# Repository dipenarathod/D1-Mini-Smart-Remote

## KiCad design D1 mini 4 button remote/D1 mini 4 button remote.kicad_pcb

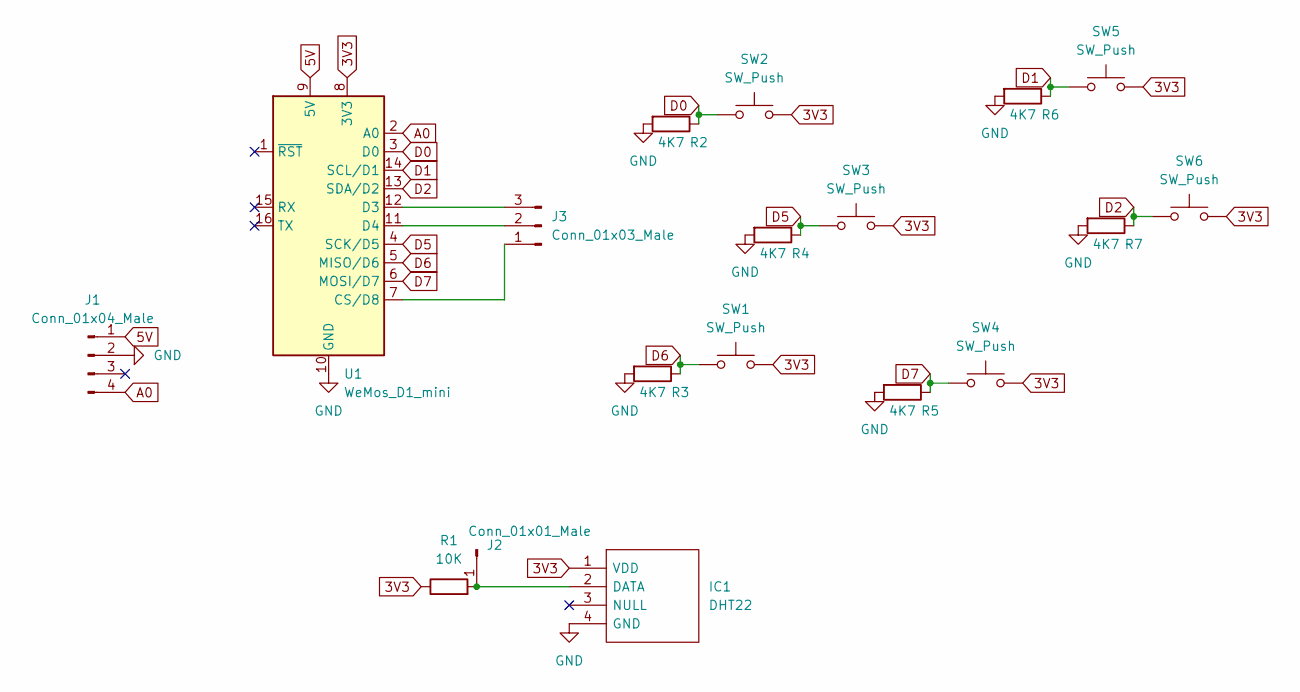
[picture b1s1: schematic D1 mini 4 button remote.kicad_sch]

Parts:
IC1: DHT22; Manufacturer_Part_Number DHT22
J1: Conn_01x04_Male; PinHeader_1x04_P2.54mm_Vertical
J2: Conn_01x01_Male; PinHeader_1x01_P2.54mm_Vertical
J3: Conn_01x03_Male; PinHeader_1x03_P2.54mm_Vertical
R1: 10K; R_Axial_DIN0207_L6.3mm_D2.5mm_P7.62mm_Horizontal
R2, R3, R4, R5, R6, R7: 4K7; R_Axial_DIN0207_L6.3mm_D2.5mm_P7.62mm_Horizontal
SW1, SW2, SW3, SW4, SW5, SW6: SW_Push; SW_PUSH_6mm
U1: WeMos_D1_mini; WEMOS_D1_mini_light

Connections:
3V3: IC1.1 (VDD), R1.1, SW1.2, SW2.2, SW3.2, SW4.2, SW5.2, SW6.2, U1.8 (3V3)
5V: J1.1, U1.9 (5V)
A0: J1.4, U1.2 (A0)
D0: R2.1, SW2.1, U1.3 (D0)
D1: R6.1, SW5.1, U1.14 (SCL/D1)
D2: R7.1, SW6.1, U1.13 (SDA/D2)
D5: R4.1, SW3.1, U1.4 (SCK/D5)
D6: R3.1, SW1.1, U1.5 (MISO/D6)
D7: R5.1, SW4.1, U1.6 (MOSI/D7)
GND: IC1.4 (GND), J1.2, R2.2, R3.2, R4.2, R5.2, R6.2, R7.2, U1.10 (GND)
unnamed: IC1.2 (DATA), J2.1, R1.2
unnamed: J3.1, U1.7 (CS/D8)
unnamed: J3.2, U1.11 (D4)
unnamed: J3.3, U1.12 (D3)

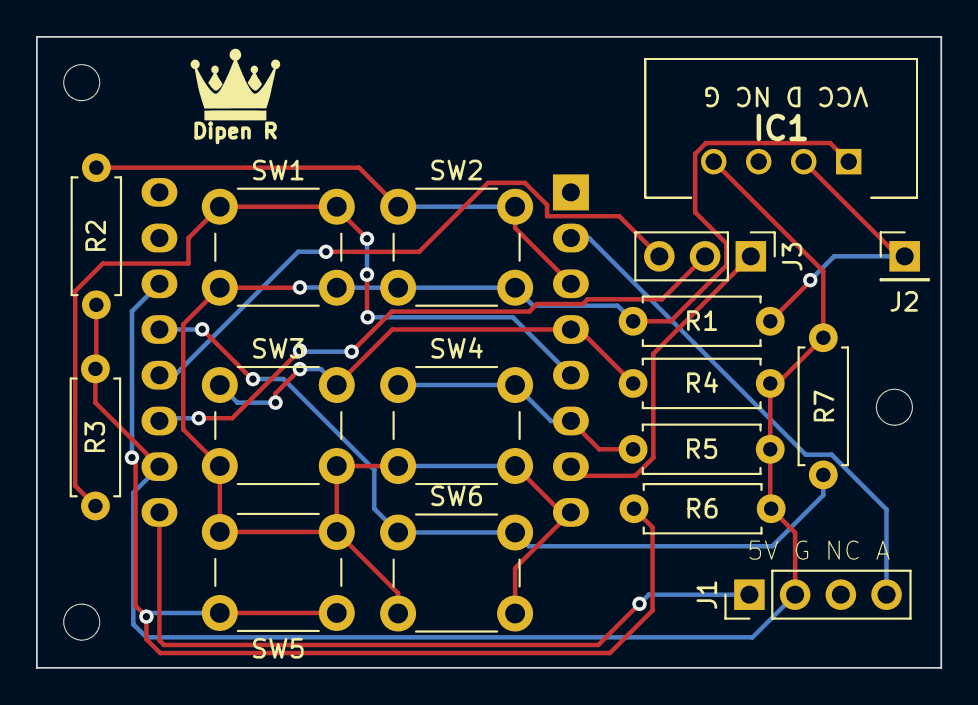
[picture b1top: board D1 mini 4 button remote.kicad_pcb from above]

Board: 2 copper layers, 50.2 x 35.1 mm, 18 parts (1 on the bottom side), 14 nets.
